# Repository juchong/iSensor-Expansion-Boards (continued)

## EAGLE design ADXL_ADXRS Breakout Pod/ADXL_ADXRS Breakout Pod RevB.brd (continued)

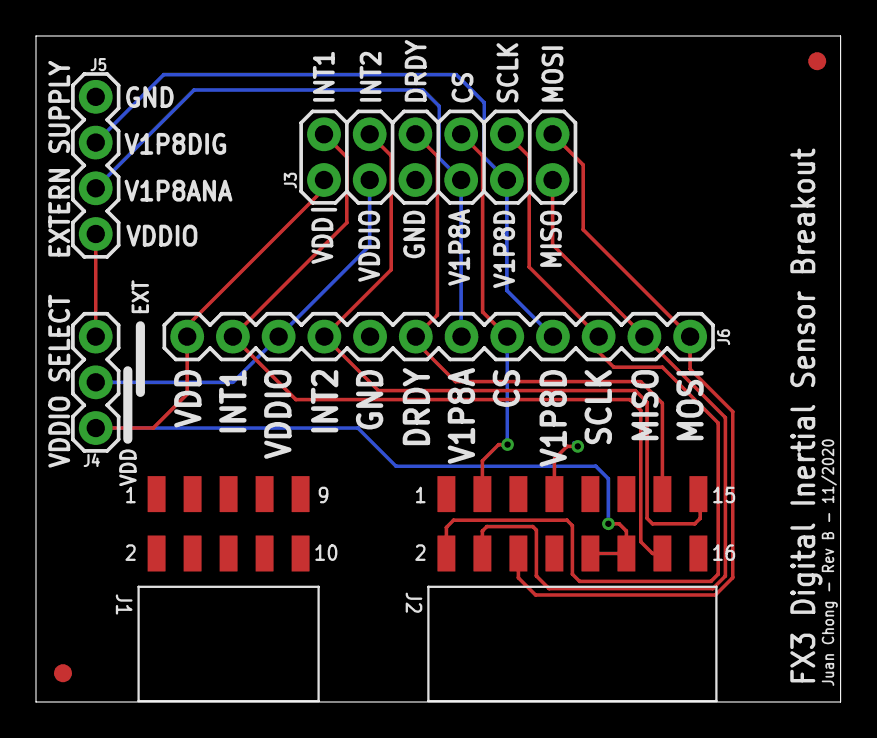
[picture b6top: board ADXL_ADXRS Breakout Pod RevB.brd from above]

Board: 2 copper layers, 44.7 x 37.0 mm, 8 parts (0 on the bottom side), 13 nets.

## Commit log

2020-11-20 Initial commit. Moving several hardware projects to GitHub
2020-11-20 Updated readme and added images
2020-11-20 Added hyperlinks to the board titles
2020-11-20 Added the SPI Extender project
2020-11-20 Added the Arduino Shield
2021-02-18 Updated the 48x,49x breakout to map new pins, added a jumper for VDDIO, and added fiducials
